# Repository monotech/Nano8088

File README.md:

Nano 8088 Rev1.1 ReadMe
----------------------------

8088 SBC based on Sergey Kiselev's Micro 8088 here:
https://github.com/skiselev/micro_8088

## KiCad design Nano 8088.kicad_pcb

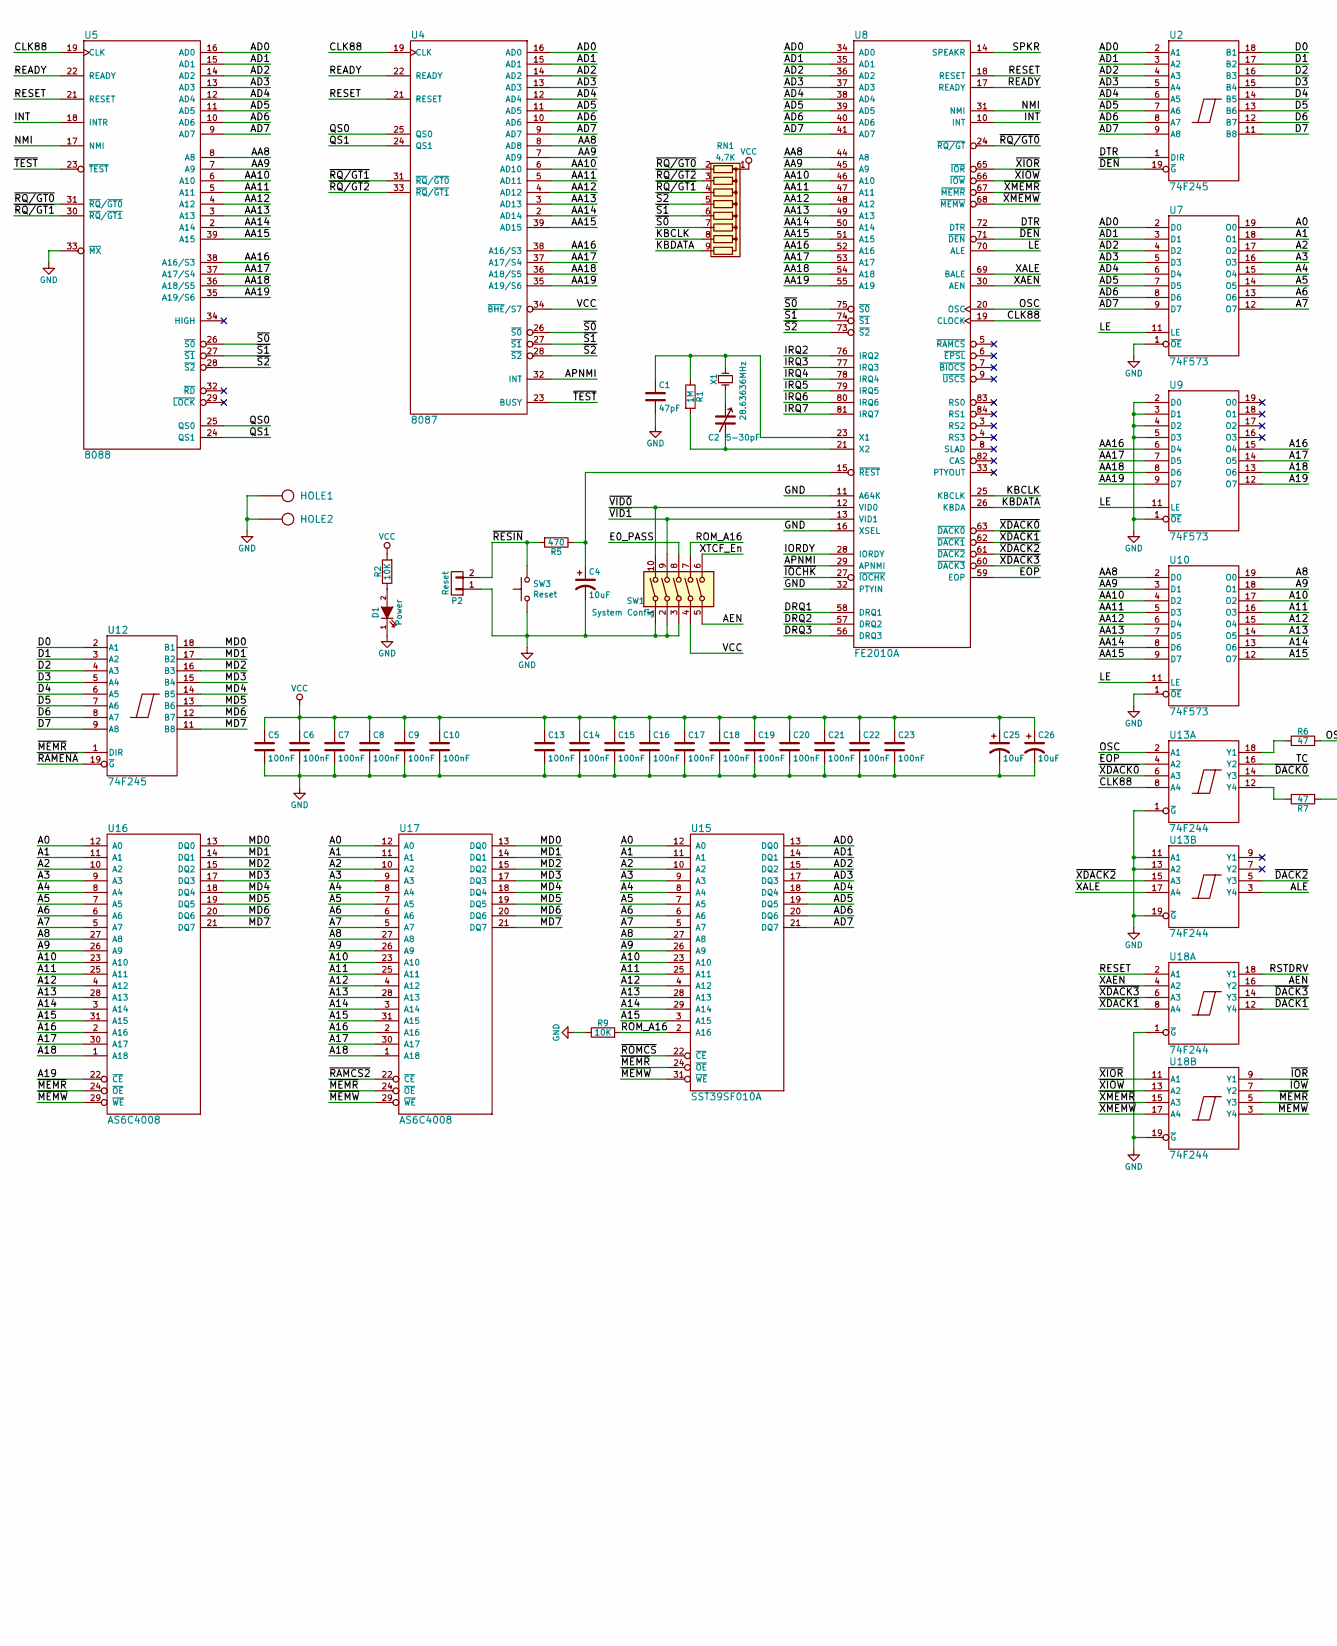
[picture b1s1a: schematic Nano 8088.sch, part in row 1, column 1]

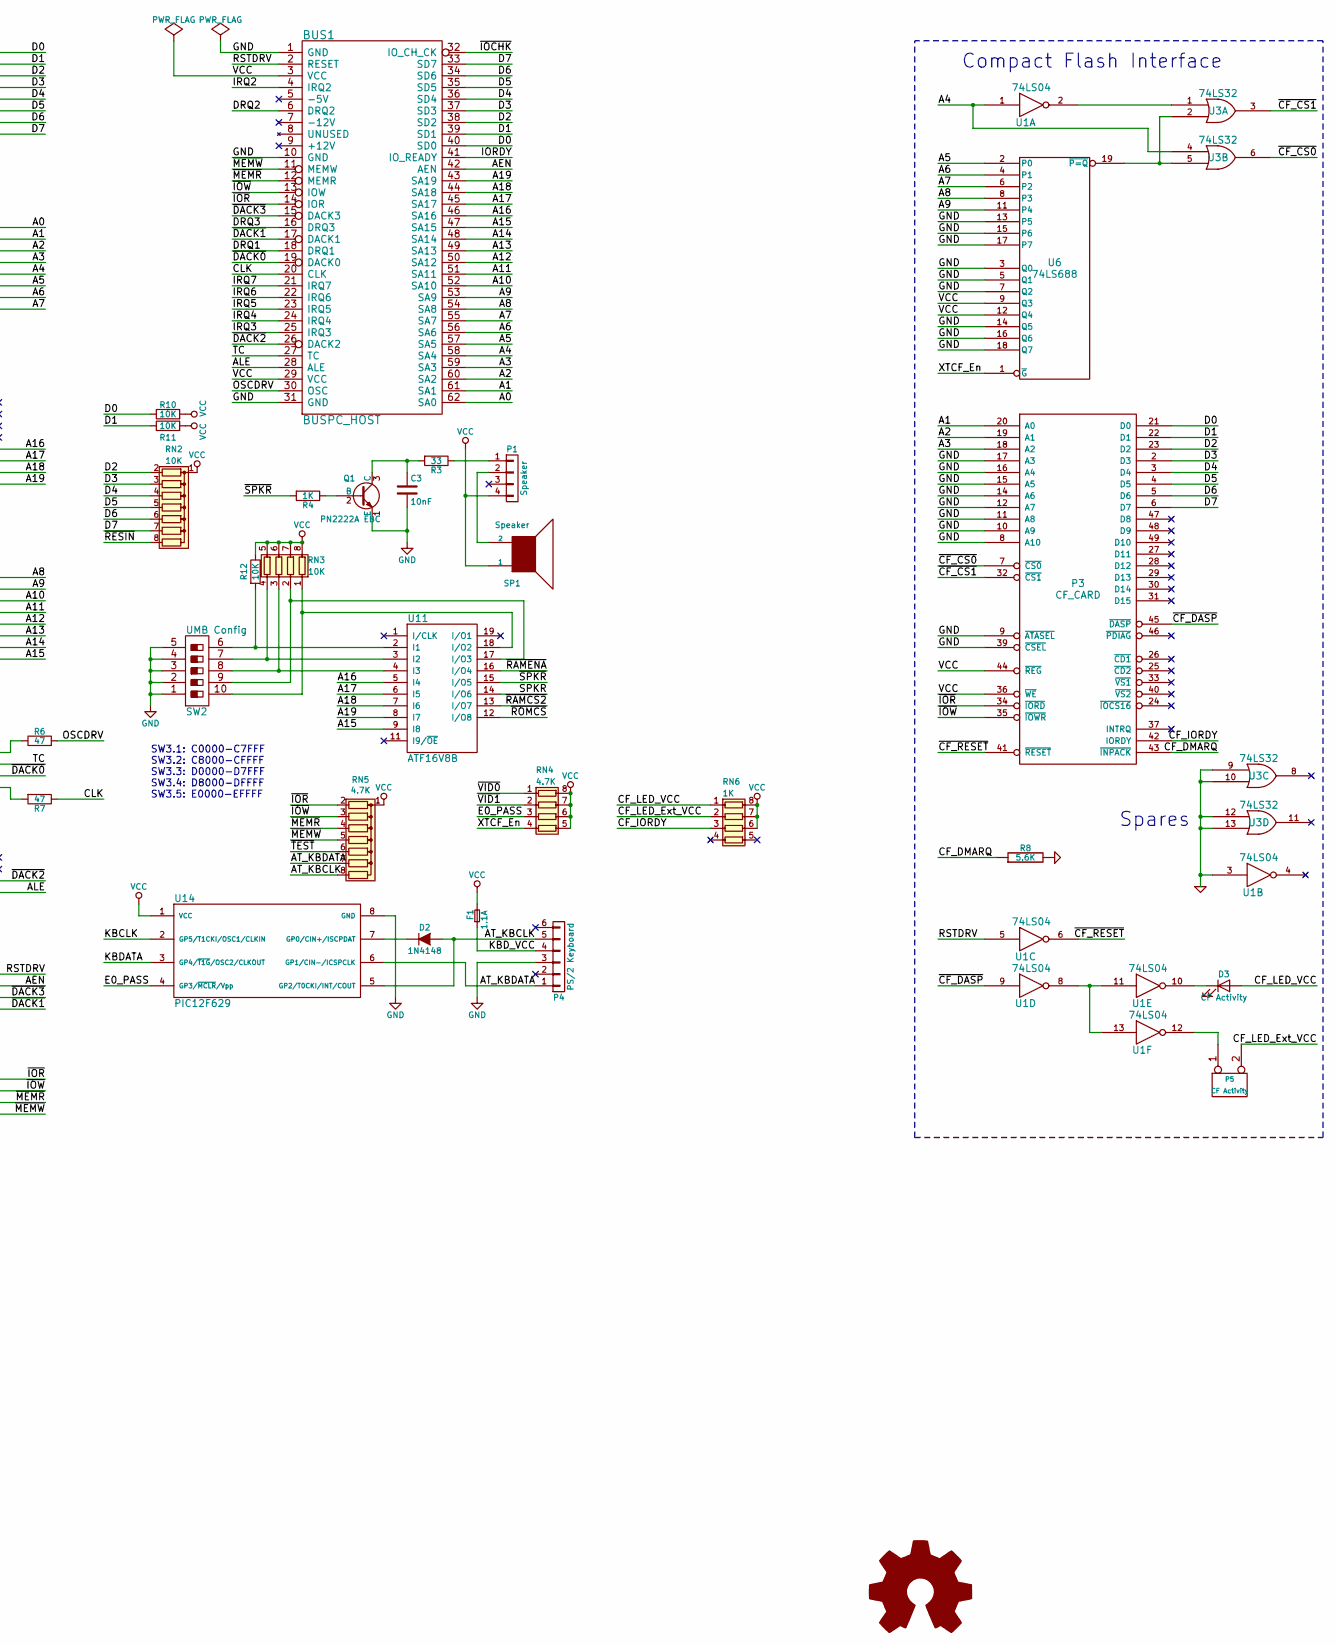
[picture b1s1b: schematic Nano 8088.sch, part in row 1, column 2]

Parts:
BUS1: BUSPC_HOST; Conn_Edge_PCB_ISA8_Micro8088
C1: 47pF; C_Disc_D4.3mm_W1.9mm_P5.00mm
C2: 5-30pF; C_Disc_D4.3mm_W1.9mm_P5.00mm
C3: 10nF; C_Disc_D4.3mm_W1.9mm_P5.00mm
C4, C25, C26: 10uF; C_0805_2012Metric_Pad1.15x1.40mm_HandSolder
C5, C6, C7, C8, C9, C10, C13, C14, C15, C16, C17, C18, C19, C20, C21, C22, C23: 100nF; C_0805_2012Metric_Pad1.15x1.40mm_HandSolder
D1: Power; LED_D3.0mm
D2: 1N4148; D_DO-34_SOD68_P7.62mm_Horizontal
D3: CF Activity; LED_D3.0mm
F1: 1.1A; C_Disc_D4.3mm_W1.9mm_P5.00mm
HOLE1, HOLE2: HOLE; MountingHole_3mm
LOGO1: Logo_Open_Hardware_Large; Monotech Logo 18mm
P1: Speaker; PinHeader_1x04_3Loaded_P2.54mm_Horizontal
P2: Reset; PinHeader_1x02_P2.54mm_Horizontal
P3: CF_CARD; CF_Slot_3M_N7E50-7516TS0884
P4: PS/2 Keyboard; Conn_Mini_DIN_6pin
P5: CF Activity; PinHeader_1x02_P2.54mm_Vertical
Q1: PN2222A EBC; TO-92_Inline_Wide
R1: 1M; R_Axial_DIN0204_L3.6mm_D1.6mm_P7.62mm_Horizontal
R2, R12: 10K; R_Axial_DIN0204_L3.6mm_D1.6mm_P2.54mm_Vertical
R3: 33; R_Axial_DIN0204_L3.6mm_D1.6mm_P2.54mm_Vertical
R4: 1K; R_Axial_DIN0204_L3.6mm_D1.6mm_P7.62mm_Horizontal
R5: 470; R_Axial_DIN0204_L3.6mm_D1.6mm_P7.62mm_Horizontal
R6, R7: 47; R_Axial_DIN0204_L3.6mm_D1.6mm_P2.54mm_Vertical
R8: 5.6K; R_Axial_DIN0204_L3.6mm_D1.6mm_P2.54mm_Vertical
R9, R10, R11: 10K; R_Axial_DIN0204_L3.6mm_D1.6mm_P7.62mm_Horizontal
RN1, RN5: 4.7K; R_Array_SIP9
RN2: 10K; R_Array_SIP8
RN3: 10K; R_Array_Convex_4x1206
RN4: 4.7K; R_Array_Convex_4x1206
RN6: 1K; R_Array_Convex_4x1206
SP1: Speaker; MagneticBuzzer_ProSignal_ABT-410-RC
SW1: System Config; SW_DIP_SPSTx05_Slide_9.78x14.88mm_W7.62mm_P2.54mm
SW2: UMB Config; SW_DIP_SPSTx05_Slide_9.78x14.88mm_W7.62mm_P2.54mm
SW3: Reset; SW_Tactile_SPST_Angled_PTS645Vx83-2LFS
U1: 74LS04; SOIC-14_3.9x8.7mm_P1.27mm
U2, U12: 74F245; SOIC-20W_7.5x12.8mm_P1.27mm
U3: 74LS32; SOIC-14_3.9x8.7mm_P1.27mm
U4: 8087; DIP-40_W15.24mm_Socket
U5: 8088; DIP-40_W15.24mm_Socket
U6: 74LS688; SOIC-20W_7.5x12.8mm_P1.27mm
U7, U9, U10: 74F573; SOIC-20W_7.5x12.8mm_P1.27mm
U8: FE2010A; PLCC-84_THT-Socket
U11: ATF16V8B; DIP-20_W7.62mm_Socket
U13, U18: 74F244; SOIC-20W_7.5x12.8mm_P1.27mm
U14: PIC12F629; DIP-8_W7.62mm_Socket
U15: SST39SF010A; DIP-32_W15.24mm_Socket
U16, U17: AS6C4008; SSOP-32_11.305x20.495mm_P1.27mm
X1: 28.63636MHz; Crystal_HC49-4H_Vertical

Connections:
/A0: BUS1.62 (SA0), U7.19 (O0), U15.12 (A0), U16.12 (A0), U17.12 (A0)
/A1: BUS1.61 (SA1), P3.20 (A0), U7.18 (O1), U15.11 (A1), U16.11 (A1), U17.11 (A1)
/A2: BUS1.60 (SA2), P3.19 (A1), U7.17 (O2), U15.10 (A2), U16.10 (A2), U17.10 (A2)
/A3: BUS1.59 (SA3), P3.18 (A2), U7.16 (O3), U15.9 (A3), U16.9 (A3), U17.9 (A3)
/A4: BUS1.58 (SA4), U1.1, U3.4, U7.15 (O4), U15.8 (A4), U16.8 (A4), U17.8 (A4)
/A5: BUS1.57 (SA5), U6.2 (P0), U7.14 (O5), U15.7 (A5), U16.7 (A5), U17.7 (A5)
/A6: BUS1.56 (SA6), U6.4 (P1), U7.13 (O6), U15.6 (A6), U16.6 (A6), U17.6 (A6)
/A7: BUS1.55 (SA7), U6.6 (P2), U7.12 (O7), U15.5 (A7), U16.5 (A7), U17.5 (A7)
/A8: BUS1.54 (SA8), U6.8 (P3), U10.19 (O0), U15.27 (A8), U16.27 (A8), U17.27 (A8)
/A9: BUS1.53 (SA9), U6.11 (P4), U10.18 (O1), U15.26 (A9), U16.26 (A9), U17.26 (A9)
/A10: BUS1.52 (SA10), U10.17 (O2), U15.23 (A10), U16.23 (A10), U17.23 (A10)
/A11: BUS1.51 (SA11), U10.16 (O3), U15.25 (A11), U16.25 (A11), U17.25 (A11)
/A12: BUS1.50 (SA12), U10.15 (O4), U15.4 (A12), U16.4 (A12), U17.4 (A12)
/A13: BUS1.49 (SA13), U10.14 (O5), U15.28 (A13), U16.28 (A13), U17.28 (A13)
/A14: BUS1.48 (SA14), U10.13 (O6), U15.29 (A14), U16.3 (A14), U17.3 (A14)
/A15: BUS1.47 (SA15), U10.12 (O7), U11.9 (I8), U15.3 (A15), U16.31 (A15), U17.31 (A15)
/A16: BUS1.46 (SA16), U9.15 (O4), U11.5 (I4), U16.2 (A16), U17.2 (A16)
/A17: BUS1.45 (SA17), U9.14 (O5), U11.6 (I5), U16.30 (A17), U17.30 (A17)
/A18: BUS1.44 (SA18), U9.13 (O6), U11.7 (I6), U16.1 (A18), U17.1 (A18)
/A19: BUS1.43 (SA19), U9.12 (O7), U11.8 (I7), U16.22 (~CE)
/AA8: U4.8 (AD8), U5.8 (A8), U8.44 (A8), U10.2 (D0)
/AA9: U4.7 (AD9), U5.7 (A9), U8.45 (A9), U10.3 (D1)
/AA10: U4.6 (AD10), U5.6 (A10), U8.46 (A10), U10.4 (D2)
/AA11: U4.5 (AD11), U5.5 (A11), U8.47 (A11), U10.5 (D3)
/AA12: U4.4 (AD12), U5.4 (A12), U8.48 (A12), U10.6 (D4)
/AA13: U4.3 (AD13), U5.3 (A13), U8.49 (A13), U10.7 (D5)
/AA14: U4.2 (AD14), U5.2 (A14), U8.50 (A14), U10.8 (D6)
/AA15: U4.39 (AD15), U5.39 (A15), U8.51 (A15), U10.9 (D7)
/AA16: U4.38 (A16/S3), U5.38 (A16/S3), U8.52 (A16), U9.6 (D4)
/AA17: U4.37 (A17/S4), U5.37 (A17/S4), U8.53 (A17), U9.7 (D5)
/AA18: U4.36 (A18/S5), U5.36 (A18/S5), U8.54 (A18), U9.8 (D6)
/AA19: U4.35 (A19/S6), U5.35 (A19/S6), U8.55 (A19), U9.9 (D7)
/AD0: U2.2 (A1), U4.16 (AD0), U5.16 (AD0), U7.2 (D0), U8.34 (AD0), U15.13 (DQ0)
/AD1: U2.3 (A2), U4.15 (AD1), U5.15 (AD1), U7.3 (D1), U8.35 (AD1), U15.14 (DQ1)
/AD2: U2.4 (A3), U4.14 (AD2), U5.14 (AD2), U7.4 (D2), U8.36 (AD2), U15.15 (DQ2)
/AD3: U2.5 (A4), U4.13 (AD3), U5.13 (AD3), U7.5 (D3), U8.37 (AD3), U15.17 (DQ3)
/AD4: U2.6 (A5), U4.12 (AD4), U5.12 (AD4), U7.6 (D4), U8.38 (AD4), U15.18 (DQ4)
/AD5: U2.7 (A6), U4.11 (AD5), U5.11 (AD5), U7.7 (D5), U8.39 (AD5), U15.19 (DQ5)
/AD6: U2.8 (A7), U4.10 (AD6), U5.10 (AD6), U7.8 (D6), U8.40 (AD6), U15.20 (DQ6)
/AD7: U2.9 (A8), U4.9 (AD7), U5.9 (AD7), U7.9 (D7), U8.41 (AD7), U15.21 (DQ7)
/AEN: BUS1.42 (AEN), SW1.5, U18.16 (Y2)
/ALE: BUS1.28 (ALE), U13.3 (Y4)
/APNMI: U4.32 (INT), U8.29 (APNMI)
/AT_KBCLK: D2.2 (A), P4.5, RN5.8 (R7), U14.5 (GP2/T0CKI/INT/COUT)
/AT_KBDATA: P4.1, RN5.7 (R6), U14.6 (GP1/CIN-/ICSPCLK)
/CF_DMARQ: P3.43 (~INPACK), R8.1
/CF_IORDY: P3.42 (IORDY), RN6.3 (R3.1)
/CF_LED_Ext_VCC: P5.2 (PM), RN6.2 (R2.1)
/CF_LED_VCC: D3.2 (A), RN6.1 (R1.1)
/CLK: BUS1.20 (CLK), R7.1
/CLK88: U4.19 (CLK), U5.19 (CLK), U8.19 (CLOCK), U13.8 (A4)
/D0: BUS1.40 (SD0), P3.21 (D0), R10.1, U2.18 (B1), U12.2 (A1)
/D1: BUS1.39 (SD1), P3.22 (D1), R11.1, U2.17 (B2), U12.3 (A2)
/D2: BUS1.38 (SD2), P3.23 (D2), RN2.2 (R1), U2.16 (B3), U12.4 (A3)
/D3: BUS1.37 (SD3), P3.2 (D3), RN2.3 (R2), U2.15 (B4), U12.5 (A4)
/D4: BUS1.36 (SD4), P3.3 (D4), RN2.4 (R3), U2.14 (B5), U12.6 (A5)
/D5: BUS1.35 (SD5), P3.4 (D5), RN2.5 (R4), U2.13 (B6), U12.7 (A6)
/D6: BUS1.34 (SD6), P3.5 (D6), RN2.6 (R5), U2.12 (B7), U12.8 (A7)
/D7: BUS1.33 (SD7), P3.6 (D7), RN2.7 (R6), U2.11 (B8), U12.9 (A8)
/DRQ1: BUS1.18 (DRQ1), U8.58 (DRQ1)
/DRQ2: BUS1.6 (DRQ2), U8.57 (DRQ2)
/DRQ3: BUS1.16 (DRQ3), U8.56 (DRQ3)
/DTR: U2.1 (DIR), U8.72 (DTR)
/E0_PASS: RN4.3 (R3.1), SW1.8, U14.4 (GP3/~MCLR~/Vpp)
/EOP: U8.59 (EOP), U13.4 (A2)
/INT: U5.18 (INTR), U8.10 (INT)
/IORDY: BUS1.41 (IO_READY), U8.28 (IORDY)
/IRQ2: BUS1.4 (IRQ2), U8.76 (IRQ2)
/IRQ3: BUS1.25 (IRQ3), U8.77 (IRQ3)
/IRQ4: BUS1.24 (IRQ4), U8.78 (IRQ4)
/IRQ5: BUS1.23 (IRQ5), U8.79 (IRQ5)
/IRQ6: BUS1.22 (IRQ6), U8.80 (IRQ6)
/IRQ7: BUS1.21 (IRQ7), U8.81 (IRQ7)
/KBCLK: RN1.8 (R7), U8.25 (KBCLK), U14.2 (GP5/T1CKI/OSC1/CLKIN)
/KBDATA: RN1.9 (R8), U8.26 (KBDA), U14.3 (GP4/~T1G~/OSC2/CLKOUT)
/KBD_VCC: F1.1, P4.4
/LE: U7.11 (LE), U8.70 (ALE), U9.11 (LE), U10.11 (LE)
/MD0: U12.18 (B1), U16.13 (DQ0), U17.13 (DQ0)
/MD1: U12.17 (B2), U16.14 (DQ1), U17.14 (DQ1)
/MD2: U12.16 (B3), U16.15 (DQ2), U17.15 (DQ2)
/MD3: U12.15 (B4), U16.17 (DQ3), U17.17 (DQ3)
/MD4: U12.14 (B5), U16.18 (DQ4), U17.18 (DQ4)
/MD5: U12.13 (B6), U16.19 (DQ5), U17.19 (DQ5)
/MD6: U12.12 (B7), U16.20 (DQ6), U17.20 (DQ6)
/MD7: U12.11 (B8), U16.21 (DQ7), U17.21 (DQ7)
/NMI: U5.17 (NMI), U8.31 (NMI)
/OSC: U8.20 (OSC), U13.2 (A1)
/OSCDRV: BUS1.30 (OSC), R6.2
/QS0: U4.25 (QS0), U5.25 (QS0)
/QS1: U4.24 (QS1), U5.24 (QS1)
/READY: U4.22 (READY), U5.22 (READY), U8.17 (READY)
/RESET: U4.21 (RESET), U5.21 (RESET), U8.18 (RESET), U18.2 (A1)
/ROM_A16: R9.2, SW1.7, U15.2 (A16)
/RSTDRV: BUS1.2 (RESET), U1.5, U18.18 (Y1)
/SPKR: U8.14 (SPEAKR), U11.14 (I/O6)
/TC: BUS1.27 (TC), U13.16 (Y2)
/XAEN: U8.30 (AEN), U18.4 (A2)
/XALE: U8.69 (BALE), U13.17 (A4)
/XTCF_En: RN4.4 (R4.1), SW1.6, U6.1 (~G)
/~CF_CS0: P3.7 (~CS0), U3.6
/~CF_CS1: P3.32 (~CS1), U3.3
/~CF_DASP: P3.45 (~DASP), U1.9
/~CF_RESET: P3.41 (~RESET), U1.6
/~DACK0: BUS1.19 (DACK0), U13.14 (Y3)
/~DACK1: BUS1.17 (DACK1), U18.12 (Y4)
/~DACK2: BUS1.26 (DACK2), U13.5 (Y3)
/~DACK3: BUS1.15 (DACK3), U18.14 (Y3)
/~DEN: U2.19 (~G), U8.71 (~DEN)
/~IOCHK: BUS1.32 (IO_CH_CK), U8.27 (~IOCHK)
/~IOR: BUS1.14 (IOR), P3.34 (~IORD), RN5.2 (R1), U18.9 (Y1)
/~IOW: BUS1.13 (IOW), P3.35 (~IOWR), RN5.3 (R2), U18.7 (Y2)
/~MEMR: BUS1.12 (MEMR), RN5.4 (R3), U12.1 (DIR), U15.24 (~OE), U16.24 (~OE), U17.24 (~OE), U18.5 (Y3)
/~MEMW: BUS1.11 (MEMW), RN5.5 (R4), U15.31 (~WE), U16.29 (~WE), U17.29 (~WE), U18.3 (Y4)
/~RAMCS2: U11.13 (I/O7), U17.22 (~CE)
/~RAMENA: U11.16 (I/O4), U12.19 (~G)
/~RESIN: P2.2, R5.2, RN2.8 (R7), SW3.2
/~ROMCS: U11.12 (I/O8), U15.22 (~CE)
/~RQ/GT0: RN1.2 (R1), U5.31 (~RQ~/~GT0~), U8.24 (~RQ/GT)
/~RQ/GT1: RN1.4 (R3), U4.31 (~RQ~/~GT0~), U5.30 (~RQ~/~GT1~)
/~RQ/GT2: RN1.3 (R2), U4.33 (~RQ~/~GT1~)
/~S0: RN1.7 (R6), U4.26 (~S0), U5.26 (~S0), U8.75 (~S0)
/~S1: RN1.6 (R5), U4.27 (~S1), U5.27 (~S1), U8.74 (~S1)
/~S2: RN1.5 (R4), U4.28 (~S2), U5.28 (~S2), U8.73 (~S2)
/~SPKR: R4.2, U11.15 (I/O5)
/~TEST: RN5.6 (R5), U4.23 (BUSY), U5.23 (~TEST)
/~VID0: RN4.1 (R1.1), SW1.10, U8.12 (VID0)
/~VID1: RN4.2 (R2.1), SW1.9, U8.13 (VID1)
/~XDACK0: U8.63 (~DACK0), U13.6 (A3)
/~XDACK1: U8.62 (~DACK1), U18.8 (A4)
/~XDACK2: U8.61 (~DACK2), U13.15 (A3)
/~XDACK3: U8.60 (~DACK3), U18.6 (A3)
/~XIOR: U8.65 (~IOR), U18.11 (A1)
/~XIOW: U8.66 (~IOW), U18.13 (A2)
/~XMEMR: U8.67 (~MEMR), U18.15 (A3)
/~XMEMW: U8.68 (~MEMW), U18.17 (A4)
GND: BUS1.1 (GND), BUS1.10 (GND), BUS1.31 (GND), C1.2, C3.2, C4.2, C5.2, C6.2, C7.2, C8.2, C9.2, C10.2, C13.2, C14.2, C15.2, C16.2, C17.2, C18.2, C19.2, C20.2, C21.2, C22.2, C23.2, C25.2, C26.2, D1.1 (K), HOLE1.1, HOLE2.1, P2.1, P3.1 (GND), P3.8 (A10), P3.9 (~ATASEL), P3.10 (A9), P3.11 (A8), P3.12 (A7), P3.14 (A6), P3.15 (A5), P3.16 (A4), P3.17 (A3), P3.39 (~CSEL), P3.50 (GND), P4.3, Q1.1 (E), R8.2, R9.1, SW1.1, SW1.2, SW1.3, SW2.1, SW2.2, SW2.3, SW2.4, SW2.5, SW3.1, U1.3, U1.7 (GND), U2.10 (GND), U3.7 (GND), U3.9, U3.10, U3.12, U3.13, U4.1 (GND), U4.20 (GND), U5.1 (GND), U5.20 (GND), U5.33 (~MX), U6.3 (Q0), U6.5 (Q1), U6.7 (Q2), U6.10 (GND), U6.13 (P5), U6.14 (Q5), U6.15 (P6), U6.16 (Q6), U6.17 (P7), U6.18 (Q7), U7.1 (~OE), U7.10 (GND), U8.2 (GND), U8.11 (A64K), U8.16 (XSEL), U8.22 (GND), U8.32 (PTYIN), U8.42 (GND), U8.64 (GND), U9.1 (~OE), U9.2 (D0), U9.3 (D1), U9.4 (D2), U9.5 (D3), U9.10 (GND), U10.1 (~OE), U10.10 (GND), U11.10 (GND), U12.10 (GND), U13.1 (~G), U13.10 (GND), U13.11 (A1), U13.13 (A2), U13.19 (~G), U14.8 (GND), U15.16 (GND), U16.16 (GND), U17.16 (GND), U18.1 (~G), U18.10 (GND), U18.19 (~G)
unnamed: C1.1, R1.1, U8.23 (X1), X1.2
unnamed: C2.1, X1.1
unnamed: C2.2, R1.2, U8.21 (X2)
unnamed: C3.1, Q1.3 (C), R3.2
unnamed: C4.1, R5.1, U8.15 (~REST)
unnamed: D1.2 (A), R2.1
unnamed: D2.1 (K), U14.7 (GP0/CIN+/ISCPDAT)
unnamed: D3.1 (K), U1.10
unnamed: P1.1, R3.1
unnamed: P1.2, SP1.2
unnamed: P5.1, U1.12
unnamed: Q1.2 (B), R4.1
unnamed: R6.1, U13.18 (Y1)
unnamed: R7.2, U13.12 (Y4)
unnamed: R12.2, SW2.6, U11.2 (I1)
unnamed: RN3.1 (R1.1), SW2.10, U11.18 (I/O2)
unnamed: RN3.2 (R2.1), SW2.9, U11.17 (I/O3)
unnamed: RN3.3 (R3.1), SW2.8, U11.4 (I3)
unnamed: RN3.4 (R4.1), SW2.7, U11.3 (I2)
unnamed: U1.2, U3.1
unnamed: U1.8, U1.11, U1.13
unnamed: U3.2, U3.5, U6.19 (~P=Q)
VCC: BUS1.3 (VCC), BUS1.29 (VCC), C5.1, C6.1, C7.1, C8.1, C9.1, C10.1, C13.1, C14.1, C15.1, C16.1, C17.1, C18.1, C19.1, C20.1, C21.1, C22.1, C23.1, C25.1, C26.1, F1.2, P1.4, P3.13 (VCC), P3.36 (~WE), P3.38 (VCC), P3.44 (~REG), R2.2, R10.2, R11.2, R12.1, RN1.1 (common), RN2.1 (common), RN3.5 (R4.2), RN3.6 (R3.2), RN3.7 (R2.2), RN3.8 (R1.2), RN4.5 (R4.2), RN4.6 (R3.2), RN4.7 (R2.2), RN4.8 (R1.2), RN5.1 (common), RN6.6 (R3.2), RN6.7 (R2.2), RN6.8 (R1.2), SP1.1, SW1.4, U1.14 (VCC), U2.20 (VCC), U3.14 (VCC), U4.34 (~BHE~/S7), U4.40 (VCC), U5.40 (VCC), U6.9 (Q3), U6.12 (Q4), U6.20 (VCC), U7.20 (VCC), U8.1 (VCC), U8.43 (VCC), U9.20 (VCC), U10.20 (VCC), U11.20 (VCC), U12.20 (VCC), U13.20 (VCC), U14.1 (VCC), U15.32 (VCC), U16.32 (VCC), U17.32 (VCC), U18.20 (VCC)

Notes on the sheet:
SW3.1: C0000-C7FFF SW3.2: C8000-CFFFF SW3.3: D0000-D7FFF SW3.4: D8000-DFFFF SW3.5: E0000-EFFFF
Spares
Compact Flash Interface

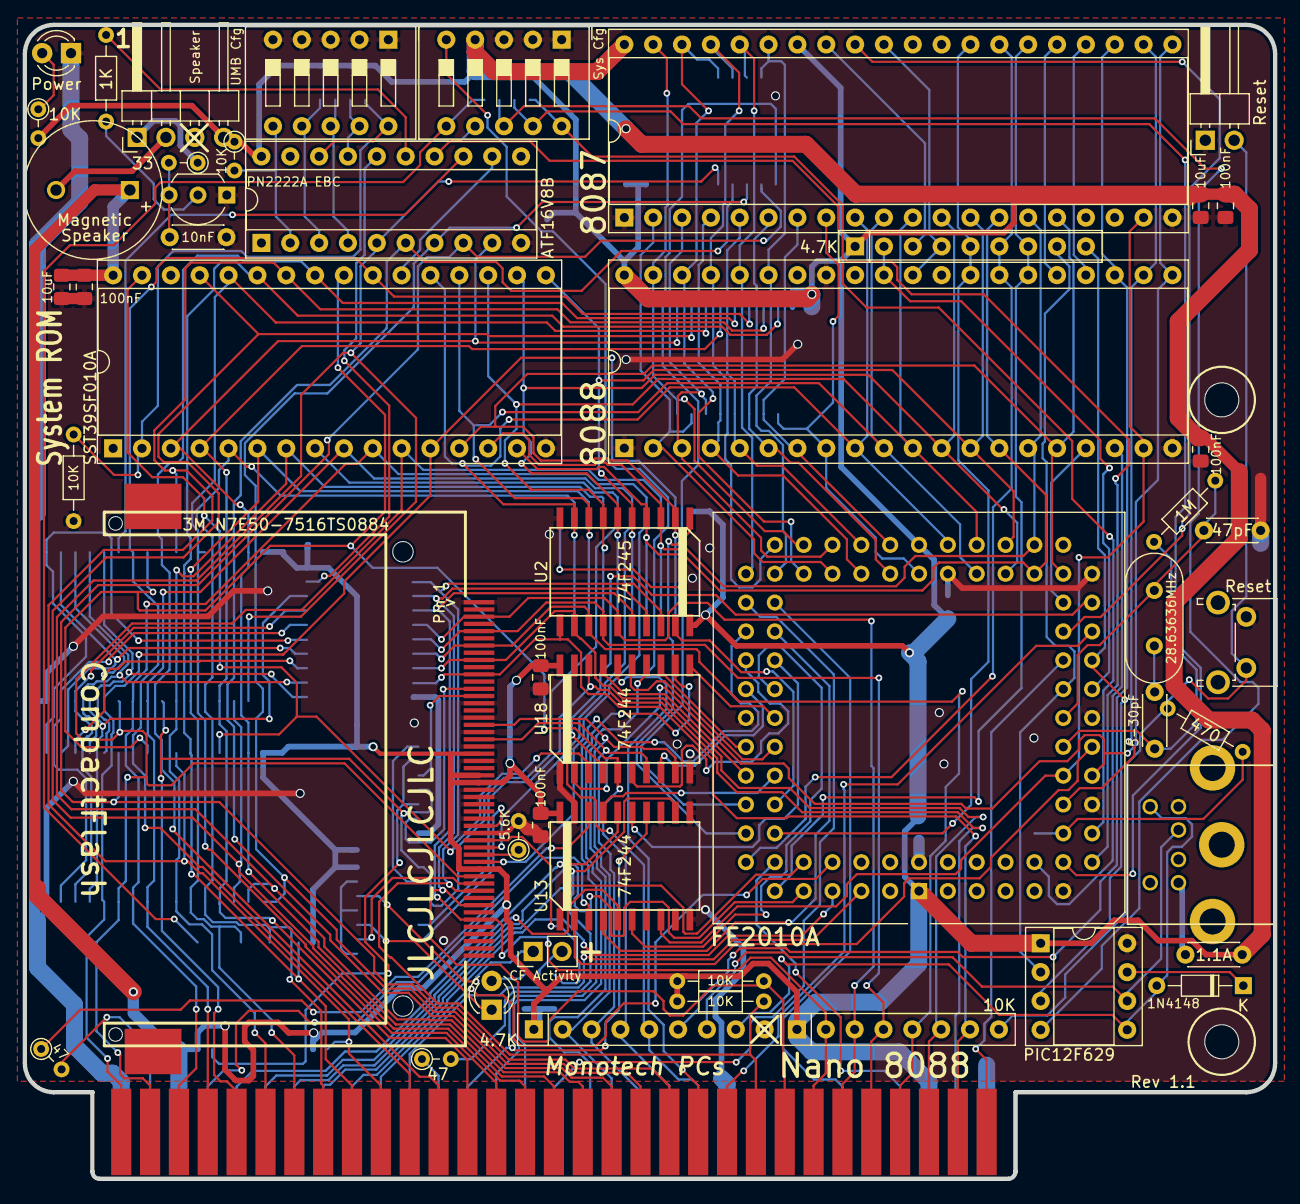
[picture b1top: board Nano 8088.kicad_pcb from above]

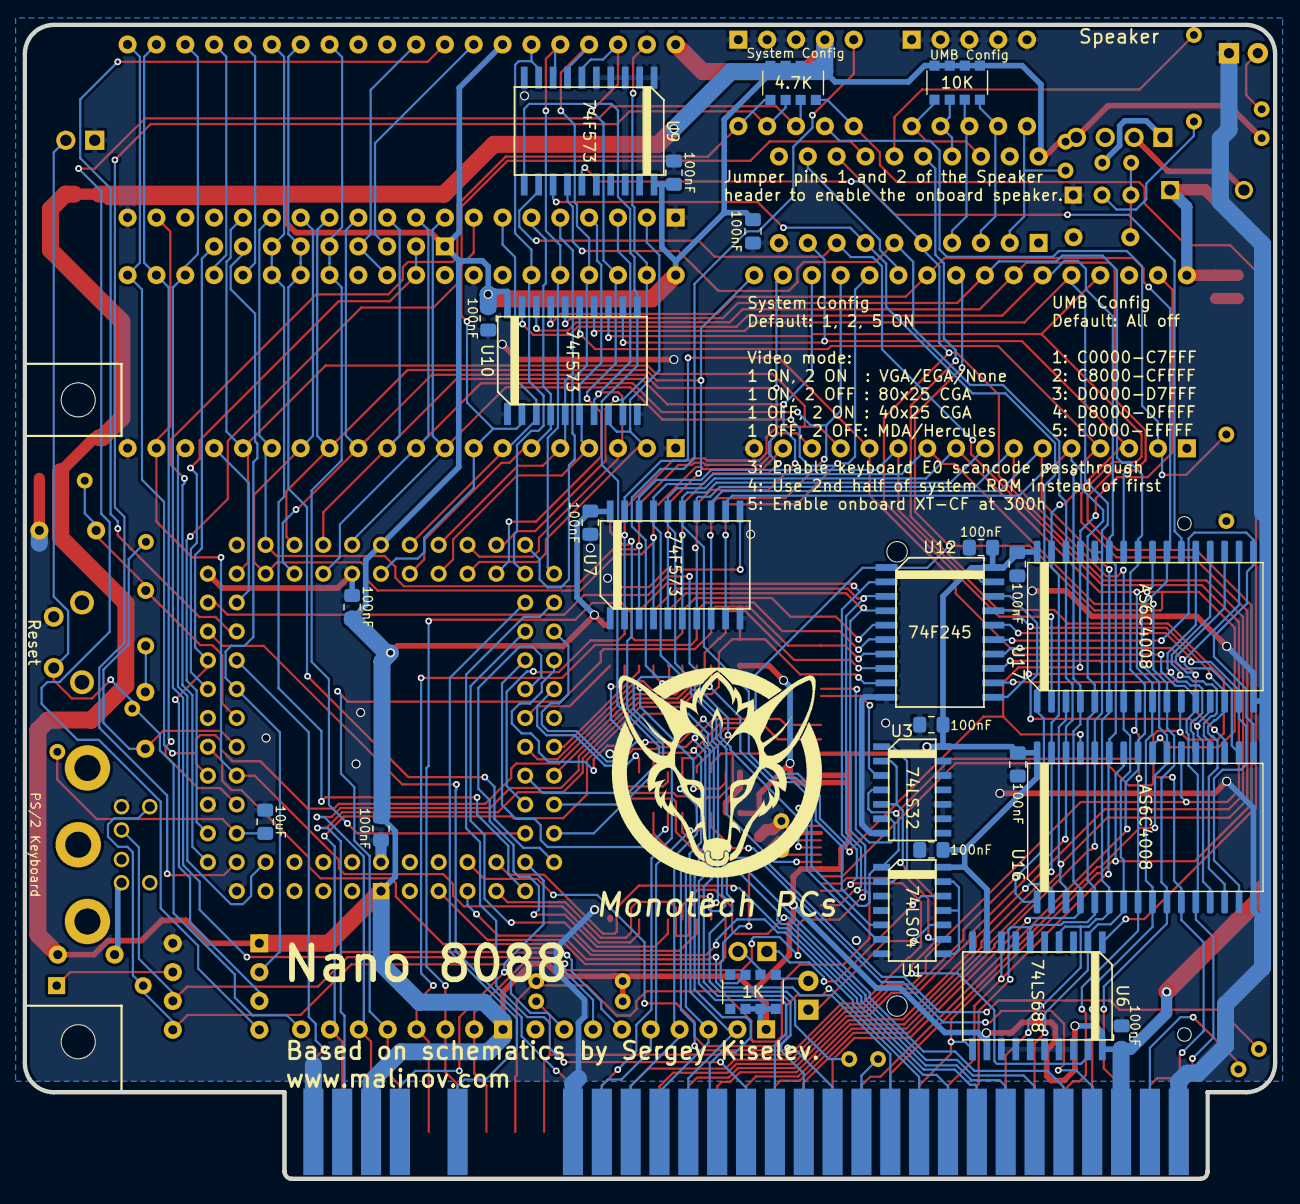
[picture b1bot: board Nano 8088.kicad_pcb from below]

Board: 2 copper layers, 110.1 x 101.6 mm, 78 parts (26 on the bottom side), 159 nets.
